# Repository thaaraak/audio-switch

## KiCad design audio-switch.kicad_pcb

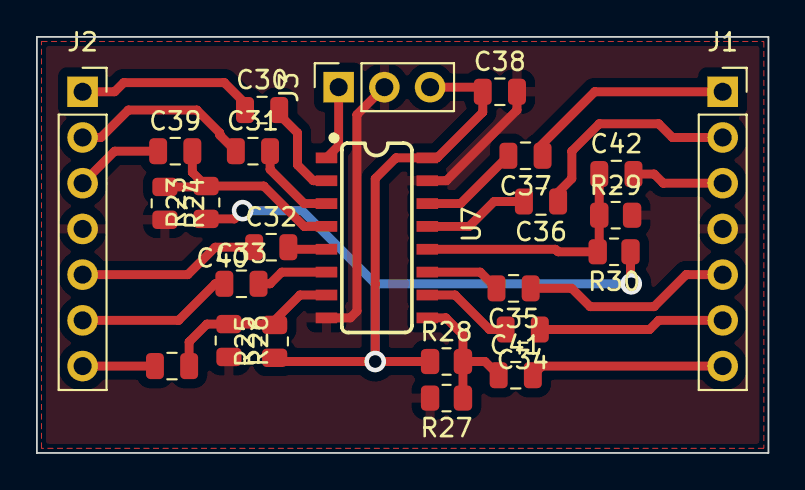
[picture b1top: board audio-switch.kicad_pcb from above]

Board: 2 copper layers, 40.6 x 23.1 mm, 25 parts (0 on the bottom side), 27 nets.

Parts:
C30, C31, C32, C33, C34, C35, C36, C37, C38, C39, C40, C41, C42: .1uF; C_0805_2012Metric
J1, J2: Conn_01x07_Female; PinSocket_1x07_P2.54mm_Vertical
J3: Conn_01x03_Female; PinSocket_1x03_P2.54mm_Vertical
R23, R24, R25, R26, R27, R28, R29, R30: 10k; R_0805_2012Metric
U7: FST3257; SO16

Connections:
+5V: C38.1, J3.3, R23.1, R25.1, R28.1, R30.1, U7.16 (VCC)
/Audio Switch/INL: C39.1, J2.3
/Audio Switch/INL1: C30.1, J2.1
/Audio Switch/INL2: C31.1, J2.2
/Audio Switch/INR: C40.1, J2.7
/Audio Switch/INR1: C32.1, J2.5
/Audio Switch/INR2: C33.1, J2.6
/Audio Switch/OUTL: C42.2, J1.3
/Audio Switch/OUTL1: C37.1, J1.1
/Audio Switch/OUTL2: C36.1, J1.2
/Audio Switch/OUTR: C41.2, J1.7
/Audio Switch/OUTR1: C35.1, J1.5
/Audio Switch/OUTR2: C34.1, J1.6
/Audio Switch/T/R: J3.1, U7.1 (S)
GND: C38.2, J1.4, J2.4, J3.2, R24.2, R26.2, R27.2, R29.2, U7.8 (GND), U7.15 (OE)
unnamed: C30.2, U7.2 (1B1)
unnamed: C31.2, U7.3 (1B2)
unnamed: C32.2, U7.5 (2B1)
unnamed: C33.2, U7.6 (2B2)
unnamed: C34.2, U7.10 (3B2)
unnamed: C35.2, U7.11 (3B1)
unnamed: C36.2, U7.13 (4B2)
unnamed: C37.2, U7.14 (4B1)
unnamed: C39.2, R23.2, R24.1, U7.4 (1A)
unnamed: C40.2, R25.2, R26.1, U7.7 (2A)
unnamed: C41.1, R27.1, R28.2, U7.9 (3A)
unnamed: C42.1, R29.1, R30.2, U7.12 (4A)
